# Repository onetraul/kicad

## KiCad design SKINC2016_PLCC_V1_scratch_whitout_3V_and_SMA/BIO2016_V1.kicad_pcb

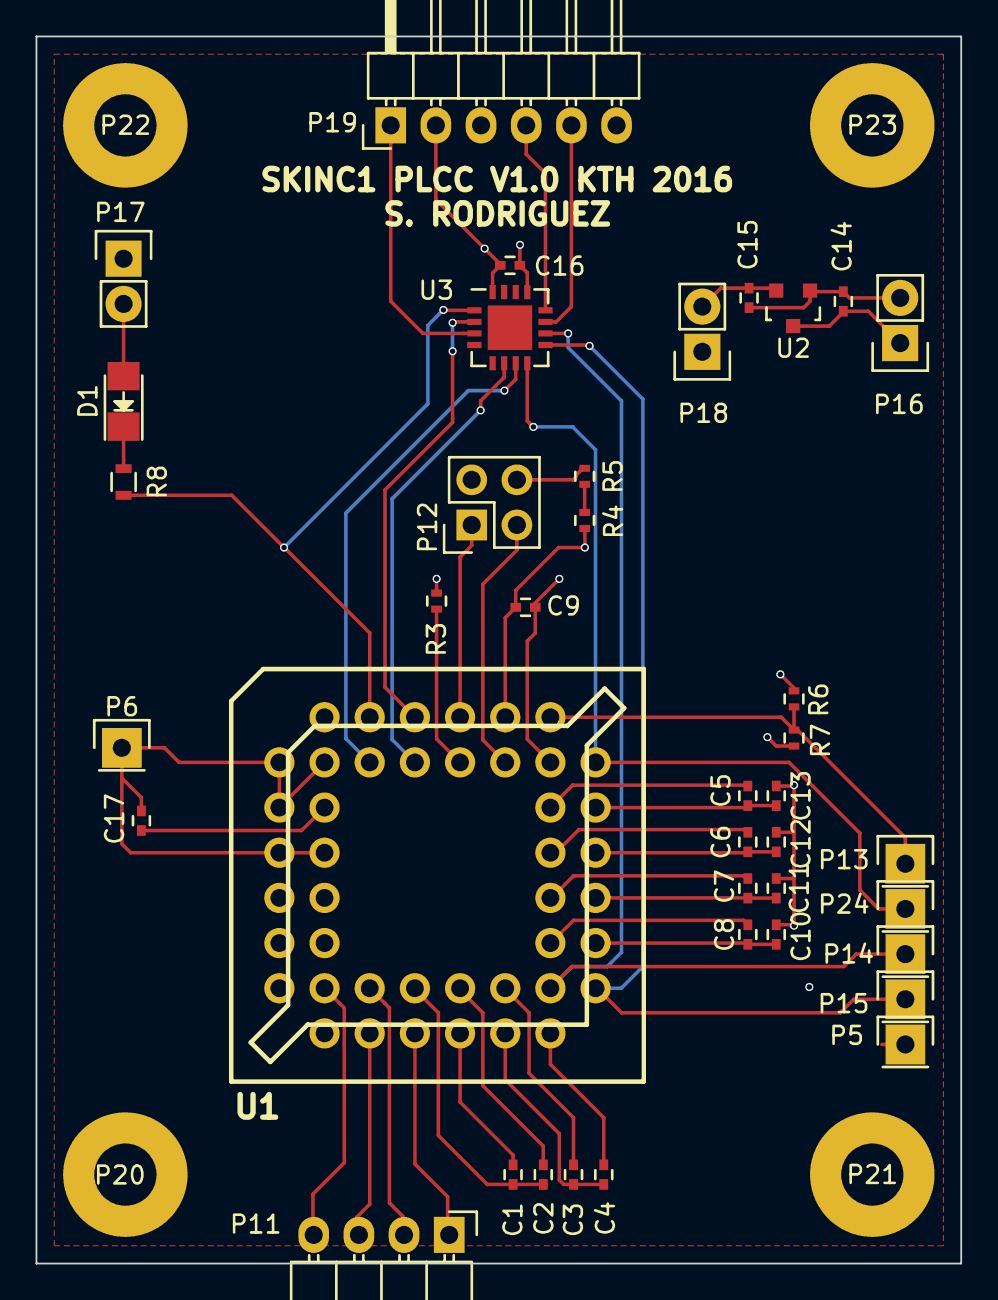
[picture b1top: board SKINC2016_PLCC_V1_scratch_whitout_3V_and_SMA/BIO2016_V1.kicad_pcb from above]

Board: 4 copper layers, 52.0 x 69.0 mm, 43 parts (0 on the bottom side), 40 nets.

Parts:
C1, C2, C3, C4: 1.5n; C_0402
C5, C6, C7, C8, C10, C11, C12, C13: 470p; C_0402
C9, C16, C17: 0.1U; C_0402
C14, C15: 1u; C_0402
D1: LED; LED_1206
P5, P6, P13, P14, P15, P24: CONN_01X01; Pin_Header_Straight_1x01
P11: CONN_01X04; Pin_Header_Angled_1x04
P12: CONN_02X02; Pin_Header_Straight_2x02
P16, P17, P18: CONN_01X02; Pin_Header_Straight_1x02
P19: CONN_01X06; Pin_Header_Angled_1x06
P20, P21, P22, P23: CONN_01X01; MountingHole_3.5mm_Pad
R3: 1M; R_0402
R4, R5: R_Small; R_0402
R6, R7: 100k; R_0402
R8: R; R_0603
U1: SKINC2016_PLCC; plcc44_pth-skt
U2: MCP1702_SOT23; SOT-23
U3: PIC16LF1823_QFN; QFN-16-1EP_4x4mm_Pitch0.65mm

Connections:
+1V8: C9.1, C16.1, C17.1, P17.1, P18.1, P19.2, R4.1, R6.1, U1.6, U1.10, U1.42, U3.16
/CFG_CLK: U1.3, U3.6
/CFG_DAT: U1.5, U3.7
/CLK_REF: U1.2, U3.2
/MCLR: P19.1, U3.3
/PGC: P19.5, U3.11
/PGD: P19.4, U3.12
/RESET_SKIN: R8.2, U1.4, U3.1
/VOUTN: P15.1, U1.29, U3.9
/VOUTP: P14.1, U1.30, U3.10
/VOUT_SE: P24.1, U1.39, U3.8
/VREF_SE: P13.1, R6.2, R7.1, U1.40
GND: C9.2, C10.2, C11.2, C12.2, C13.2, C14.2, C15.2, C16.2, C17.2, P5.1, P6.1, P12.2, P16.2, P19.3, R3.1, R7.2, U1.7, U1.8, U1.9, U1.11, U1.12, U1.41, U2.1, U3.13
unnamed: C1.1, U1.24
unnamed: C1.2, C2.2, U1.23
unnamed: C2.1, U1.25
unnamed: C3.1, U1.27
unnamed: C3.2, C4.2, U1.26
unnamed: C4.1, U1.28
unnamed: C5.2, U1.38
unnamed: C6.2, U1.36
unnamed: C7.2, U1.34
unnamed: C8.2, U1.32
unnamed: C8.1, C10.1, U1.31
unnamed: C7.1, C11.1, U1.33
unnamed: C6.1, C12.1, U1.35
unnamed: C5.1, C13.1, U1.37
unnamed: C14.1, P16.1, U2.3
unnamed: C15.1, P18.2, U2.2
unnamed: D1.1, R8.1
unnamed: D1.2, P17.2
unnamed: P11.1, U1.22
unnamed: P11.2, U1.21
unnamed: P11.3, U1.20
unnamed: P11.4, U1.19
unnamed: P12.1, U1.44
unnamed: P12.3, U1.43
unnamed: P12.4, R5.2
unnamed: R3.2, U1.1
unnamed: R4.2, R5.1

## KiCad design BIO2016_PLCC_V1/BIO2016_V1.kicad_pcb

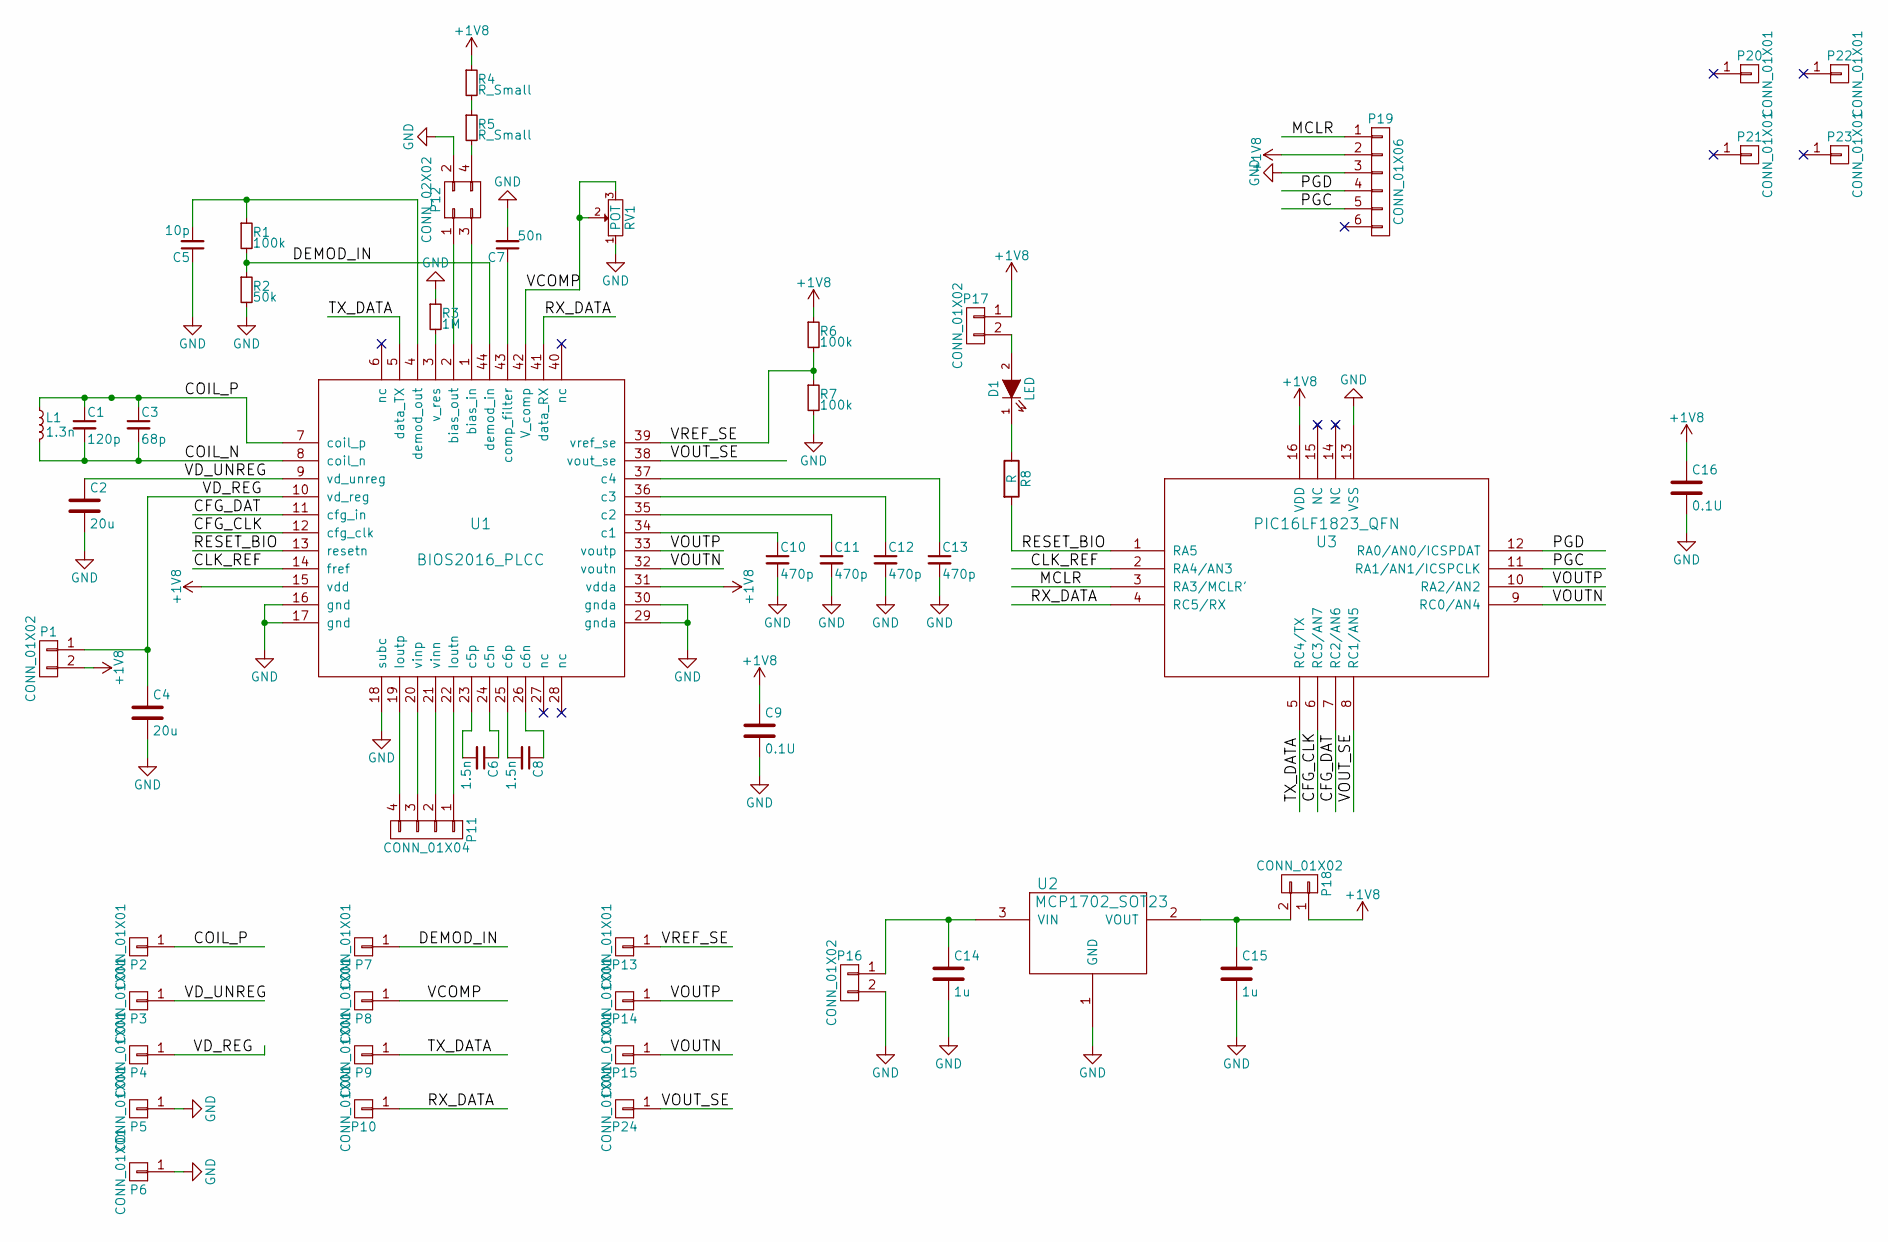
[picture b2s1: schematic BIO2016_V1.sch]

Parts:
C1: 120p; C_0402
C2, C4: 20u; C_0603
C3: 68p; C_0402
C5: 10p; C_0402
C6, C8: 1.5n; C_0402
C7: 50n; C_0402
C9, C16: 0.1U; C_0402
C10, C11, C12, C13: 470p; C_0402
C14, C15: 1u; C_0402
D1: LED; LED_1206
L1: 1.3n; Socket_Strip_Straight_1x02
P1, P16, P17, P18: CONN_01X02; Pin_Header_Straight_1x02
P2, P3, P4, P5, P6, P7, P8, P9, P10, P13, P14, P15, P24: CONN_01X01; Pin_Header_Straight_1x01
P11: CONN_01X04; Pin_Header_Angled_1x04
P12: CONN_02X02; Pin_Header_Straight_2x02
P19: CONN_01X06; Pin_Header_Angled_1x06
P20, P21, P22, P23: CONN_01X01; MountingHole_3.5mm_Pad
R1, R6, R7: 100k; R_0402
R2: 50k; R_0402
R3: 1M; R_0402
R4, R5: R_Small; R_0402
R8: R; R_0603
RV1: POT; Potentiometer_Bourns_3296W_3-8Zoll_Inline_ScrewUp
U1: BIOS2016_PLCC; plcc44_pth-skt
U2: MCP1702_SOT23; SOT-23
U3: PIC16LF1823_QFN; QFN-16-1EP_4x4mm_Pitch0.65mm

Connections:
+1V8: C9.1, C16.1, P1.2, P17.1, P18.1, P19.2, R4.1, R6.1, U1.15 (vdd), U1.31 (vdda), U3.16 (VDD)
/CFG_CLK: U1.12 (cfg_clk), U3.6 (RC3/AN7)
/CFG_DAT: U1.11 (cfg_in), U3.7 (RC2/AN6)
/CLK_REF: U1.14 (fref), U3.2 (RA4/AN3)
/COIL_N: C1.2, C3.2, L1.2, U1.8 (coil_n)
/COIL_P: C1.1, C3.1, L1.1, P2.1, U1.7 (coil_p)
/DEMOD_IN: P7.1, R1.2, R2.1, U1.44 (demod_in)
/MCLR: P19.1, U3.3 (RA3/MCLR')
/PGC: P19.5, U3.11 (RA1/AN1/ICSPCLK)
/PGD: P19.4, U3.12 (RA0/AN0/ICSPDAT)
/RESET_BIO: R8.2, U1.13 (resetn), U3.1 (RA5)
/RX_DATA: P10.1, U1.41 (data_RX), U3.4 (RC5/RX)
/TX_DATA: P9.1, U1.5 (data_TX), U3.5 (RC4/TX)
/VCOMP: P8.1, RV1.2, RV1.3, U1.42 (V_comp)
/VD_REG: C4.1, P1.1, P4.1, U1.10 (vd_reg)
/VD_UNREG: C2.1, P3.1, U1.9 (vd_unreg)
/VOUTN: P15.1, U1.32 (voutn), U3.9 (RC0/AN4)
/VOUTP: P14.1, U1.33 (voutp), U3.10 (RA2/AN2)
/VOUT_SE: P24.1, U1.38 (vout_se), U3.8 (RC1/AN5)
/VREF_SE: P13.1, R6.2, R7.1, U1.39 (vref_se)
GND: C2.2, C4.2, C5.1, C7.2, C9.2, C10.2, C11.2, C12.2, C13.2, C14.2, C15.2, C16.2, P5.1, P6.1, P12.2, P16.2, P19.3, R2.2, R3.1, R7.2, RV1.1, U1.16 (gnd), U1.17 (gnd), U1.18 (subc), U1.29 (gnda), U1.30 (gnda), U2.1 (GND), U3.13 (VSS)
unnamed: C5.2, R1.1, U1.4 (demod_out)
unnamed: C6.1, U1.24 (c5n)
unnamed: C6.2, U1.23 (c5p)
unnamed: C7.1, U1.43 (comp_filter)
unnamed: C8.1, U1.26 (c6n)
unnamed: C8.2, U1.25 (c6p)
unnamed: C10.1, U1.34 (c1)
unnamed: C11.1, U1.35 (c2)
unnamed: C12.1, U1.36 (c3)
unnamed: C13.1, U1.37 (c4)
unnamed: C14.1, P16.1, U2.3 (VIN)
unnamed: C15.1, P18.2, U2.2 (VOUT)
unnamed: D1.1 (K), R8.1
unnamed: D1.2 (A), P17.2
unnamed: P11.1, U1.22 (Ioutn)
unnamed: P11.2, U1.21 (vinn)
unnamed: P11.3, U1.20 (vinp)
unnamed: P11.4, U1.19 (Ioutp)
unnamed: P12.1, U1.2 (bias_out)
unnamed: P12.3, U1.1 (bias_in)
unnamed: P12.4, R5.2
unnamed: R3.2, U1.3 (v_res)
unnamed: R4.2, R5.1

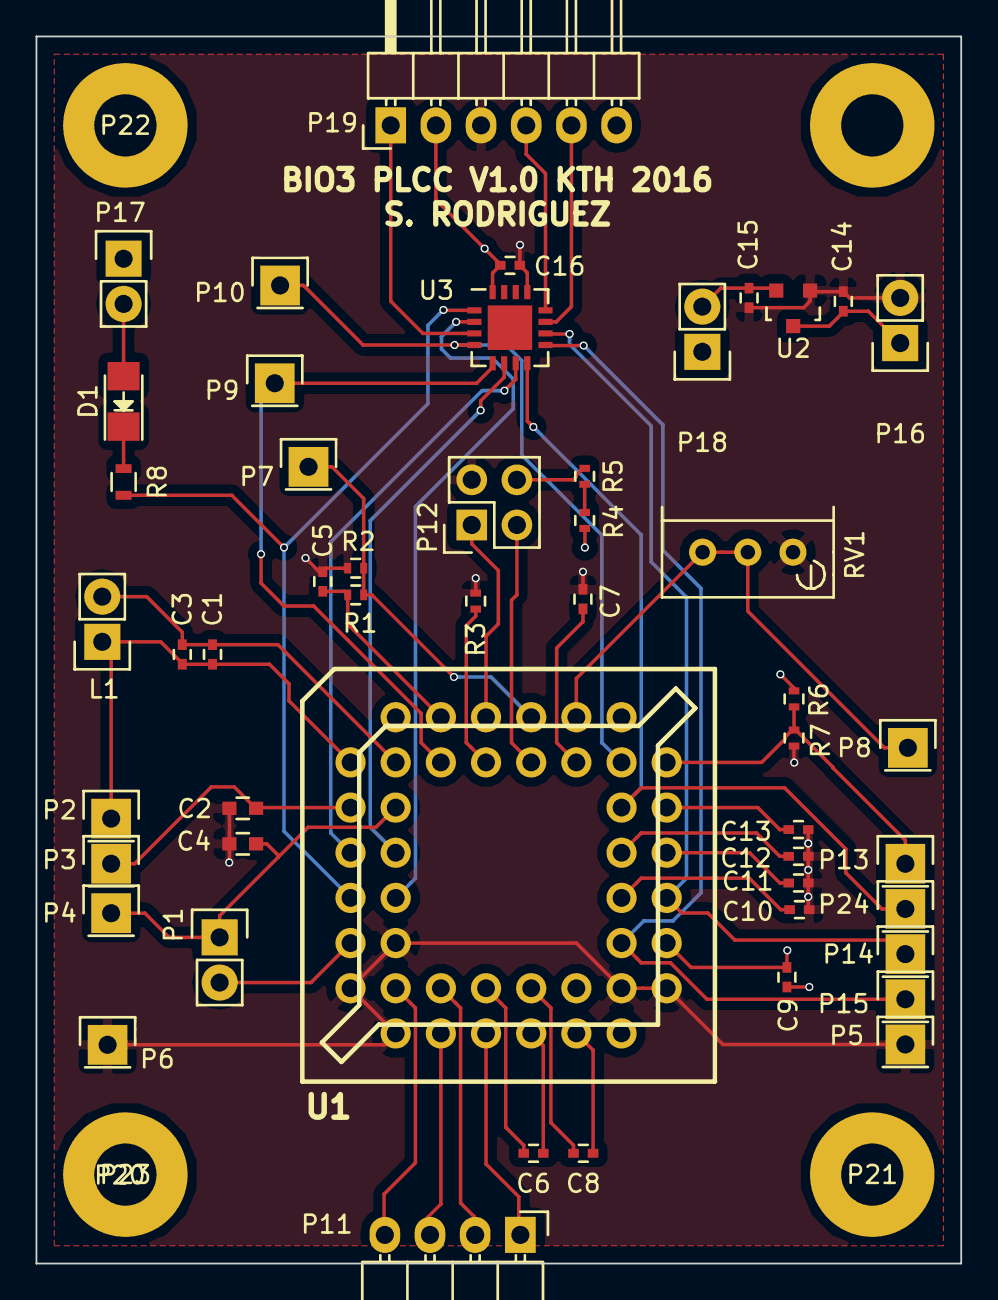
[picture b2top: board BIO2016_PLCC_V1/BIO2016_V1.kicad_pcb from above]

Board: 4 copper layers, 52.0 x 69.0 mm, 54 parts (0 on the bottom side), 44 nets.
